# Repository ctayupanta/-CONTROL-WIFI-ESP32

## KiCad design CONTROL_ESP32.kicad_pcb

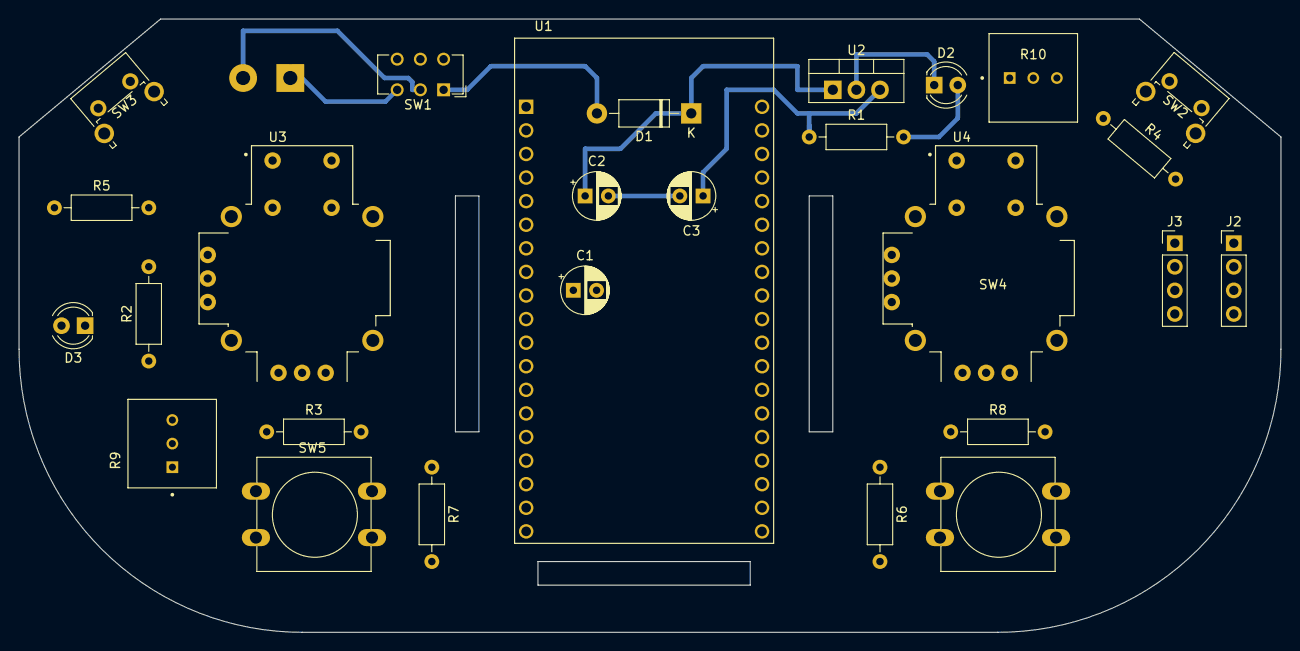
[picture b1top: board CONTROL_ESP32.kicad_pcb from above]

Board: 2 copper layers, 135.9 x 66.0 mm, 28 parts (1 on the bottom side), 25 nets.

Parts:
C1: C_Polarized_Small_US; CP_Radial_D5.0mm_P2.50mm
C2, C3: C_Polarized_Small; CP_Radial_D5.0mm_P2.50mm
D1: 1N4004; D_DO-41_SOD81_P10.16mm_Horizontal
D2, D3: LED; LED_D4.0mm
J1: Screw_Terminal_01x02; TerminalBlock_bornier-2_P5.08mm
J2, J3: Screw_Terminal_01x04; PinHeader_1x04_P2.54mm_Vertical
R1, R3, R8: R; R_Axial_DIN0207_L6.3mm_D2.5mm_P10.16mm_Horizontal
R2: 330; R_Axial_DIN0207_L6.3mm_D2.5mm_P10.16mm_Horizontal
R4, R5, R6, R7: 4.7k; R_Axial_DIN0207_L6.3mm_D2.5mm_P10.16mm_Horizontal
R9, R10: COM-09806; TRIM_COM-09806
SW1: SW_Push_SPDT; SW_CuK_JS202011CQN_DPDT_Straight
SW2, SW3: SW_Push; SW_Tactile_SPST_Angled_PTS645Vx83-2LFS
SW4, SW5: SW_Push; SW_PUSH-12mm
U1: ESP32-DEVKITC-32D; MODULE_ESP32-DEVKITC-32D
U2: LM7805_TO220; TO-220-3_Vertical
U3, U4: COM-09032; XDCR_COM-09032

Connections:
+3V3: C1.1, J2.1, J3.1, R3.1, R4.1, R5.1, R6.1, R7.1, R8.1, R9.1, R10.1, U1.1 (3V3), U3.H1 (H+), U3.V1 (V+), U4.H1 (H+), U4.V1 (V+)
GND: C1.2, C2.2, C3.2, D2.1 (K), D3.1 (K), J1.1, J2.2, J3.2, R9.3, R10.3, SW1.3 (C), SW2.2, SW3.2, SW4.2, SW5.2, U1.2 (EN), U1.14 (GND1), U1.20 (GND3), U1.26 (GND2), U2.2 (GND), U3.B2A (SEL-), U3.H3 (H-), U3.V3 (V-), U4.B2A (SEL-), U4.H3 (H-), U4.V3 (V-)
IO2: R4.2, SW2.1, U1.34 (IO2)
IO4: R9.2, U1.32 (IO4)
IO12: R7.2, SW5.1, U1.13 (IO12)
IO13: R5.2, SW3.1, U1.15 (IO13)
IO15: R6.2, SW4.1, U1.35 (IO15)
IO23: R2.1, U1.21 (IO23)
IO25: R8.2, U1.9 (IO25), U4.B1A (SEL+)
IO26: R3.2, U1.10 (IO26), U3.B1A (SEL+)
IO32: U1.7 (IO32), U3.V2 (V)
IO33: U1.8 (IO33), U4.H2 (H)
IO34: U1.5 (IO34), U4.V2 (V)
IO35: U1.6 (IO35), U3.H2 (H)
IO36: R10.2, U1.3 (SENSOR_VP)
unnamed: C2.1, D1.1 (K), U2.1 (VI)
unnamed: C3.1, R1.1, U2.3 (VO)
unnamed: D1.2 (A), SW1.1 (A)
unnamed: D2.2 (A), R1.2
unnamed: D3.2 (A), R2.2
unnamed: J1.2, SW1.2 (B)
RX: J3.3, U1.24 (RXD0)
SCL: J2.4, U1.22 (IO22)
SDA: J2.3, U1.25 (IO21)
TX: J3.4, U1.23 (TXD0)

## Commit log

2022-09-06 Subiendo primera version
2022-09-06 Un pequeño Cambio
2022-09-06 add copia
2022-09-06 add imagen
